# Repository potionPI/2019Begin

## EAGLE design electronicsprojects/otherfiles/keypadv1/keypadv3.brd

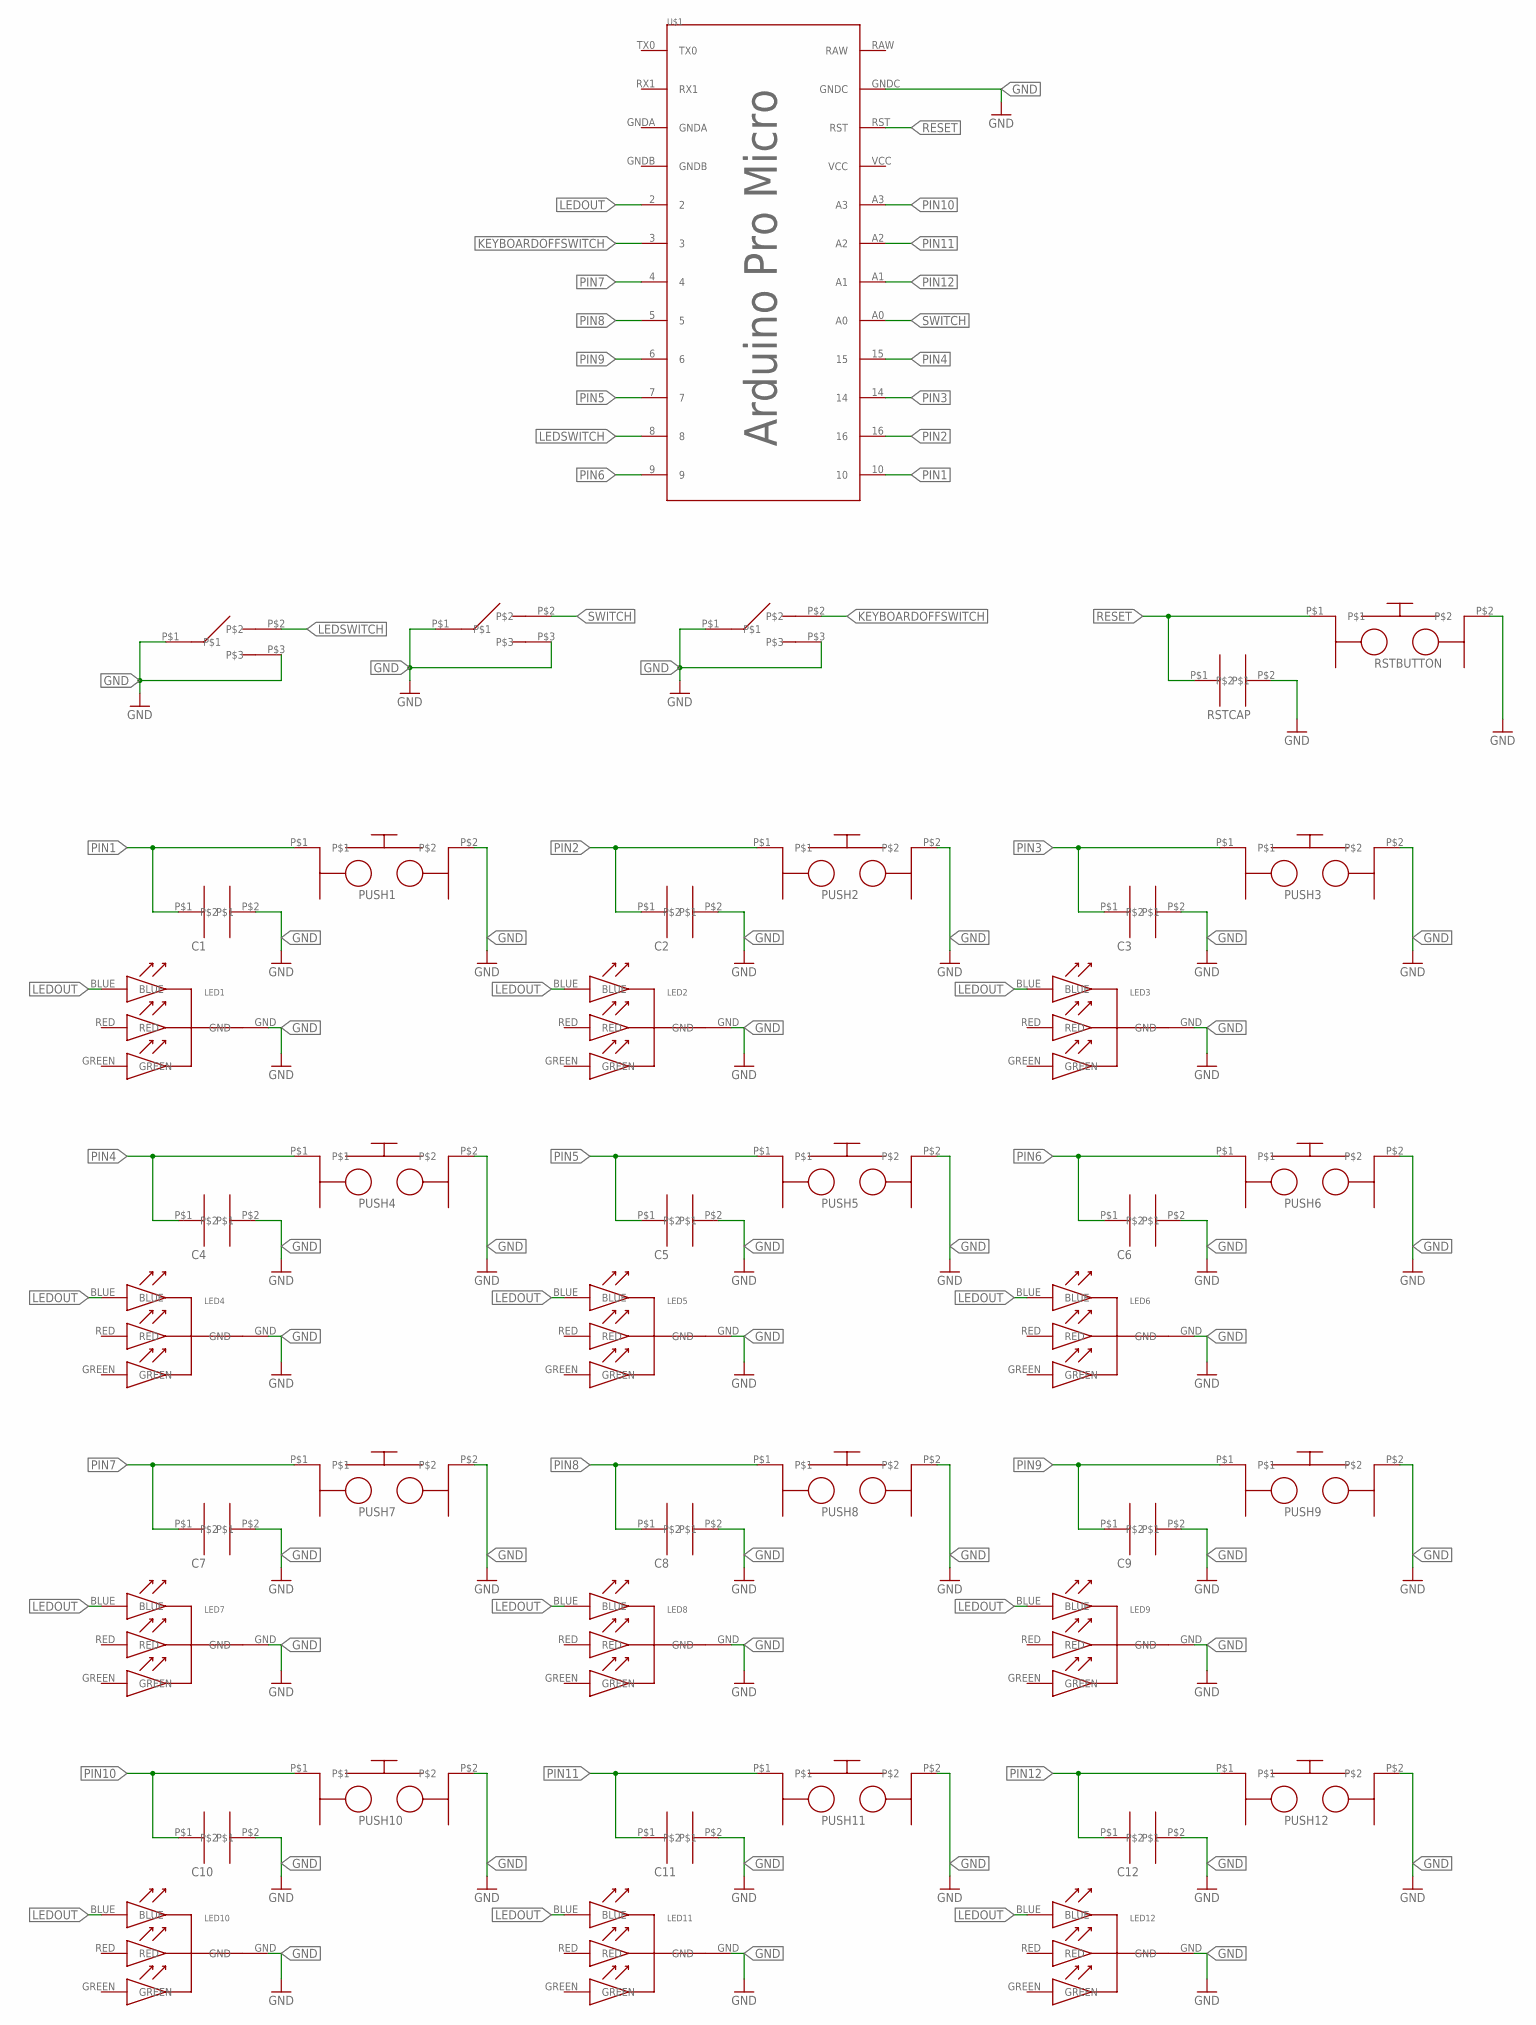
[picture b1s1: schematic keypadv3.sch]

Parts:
C1, C2, C3, C4, C5, C6, C7, C8, C9, C10, C11, C12: CERAMICCAP; CERAMICCAPACITOR
LED1, LED2, LED3, LED4, LED5, LED6, LED7, LED8, LED9, LED10, LED11, LED12: RGBLED5MMCOMMONCATHODE; LEADSPREAD
PUSH1, PUSH2, PUSH3, PUSH4, PUSH5, PUSH6, PUSH7, PUSH8, PUSH9, PUSH10, PUSH11, PUSH12: 2LEADS
RSTBUTTON: 2LEADS
RSTCAP: CERAMICCAP; CERAMICCAPACITOR
SWITCH1, SWITCH2, SWITCH3: SWITCH; THREEPINSWITCH
U$1: ARDUINOPROMICRO; ARDUINO_PRO_MICRO

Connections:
GND: C1.P$2, C2.P$2, C3.P$2, C4.P$2, C5.P$2, C6.P$2, C7.P$2, C8.P$2, C9.P$2, C10.P$2, C11.P$2, C12.P$2, LED1.GND, LED2.GND, LED3.GND, LED4.GND, LED5.GND, LED6.GND, LED7.GND, LED8.GND, LED9.GND, LED10.GND, LED11.GND, LED12.GND, PUSH1.P$2, PUSH2.P$2, PUSH3.P$2, PUSH4.P$2, PUSH5.P$2, PUSH6.P$2, PUSH7.P$2, PUSH8.P$2, PUSH9.P$2, PUSH10.P$2, PUSH11.P$2, PUSH12.P$2, RSTBUTTON.P$2, RSTCAP.P$2, SWITCH1.P$1, SWITCH1.P$3, SWITCH2.P$1, SWITCH2.P$3, SWITCH3.P$1, SWITCH3.P$3, U$1.GNDC
KEYBOARDOFFSWITCH: SWITCH2.P$2, U$1.3
LEDOUT: LED1.BLUE, LED2.BLUE, LED3.BLUE, LED4.BLUE, LED5.BLUE, LED6.BLUE, LED7.BLUE, LED8.BLUE, LED9.BLUE, LED10.BLUE, LED11.BLUE, LED12.BLUE, U$1.2
LEDSWITCH: SWITCH1.P$2, U$1.8
PIN1: C1.P$1, PUSH1.P$1, U$1.10
PIN2: C2.P$1, PUSH2.P$1, U$1.16
PIN3: C3.P$1, PUSH3.P$1, U$1.14
PIN4: C4.P$1, PUSH4.P$1, U$1.15
PIN5: C5.P$1, PUSH5.P$1, U$1.7
PIN6: C6.P$1, PUSH6.P$1, U$1.9
PIN7: C7.P$1, PUSH7.P$1, U$1.4
PIN8: C8.P$1, PUSH8.P$1, U$1.5
PIN9: C9.P$1, PUSH9.P$1, U$1.6
PIN10: C10.P$1, PUSH10.P$1, U$1.A3
PIN11: C11.P$1, PUSH11.P$1, U$1.A2
PIN12: C12.P$1, PUSH12.P$1, U$1.A1
RESET: RSTBUTTON.P$1, RSTCAP.P$1, U$1.RST
SWITCH: SWITCH3.P$2, U$1.A0

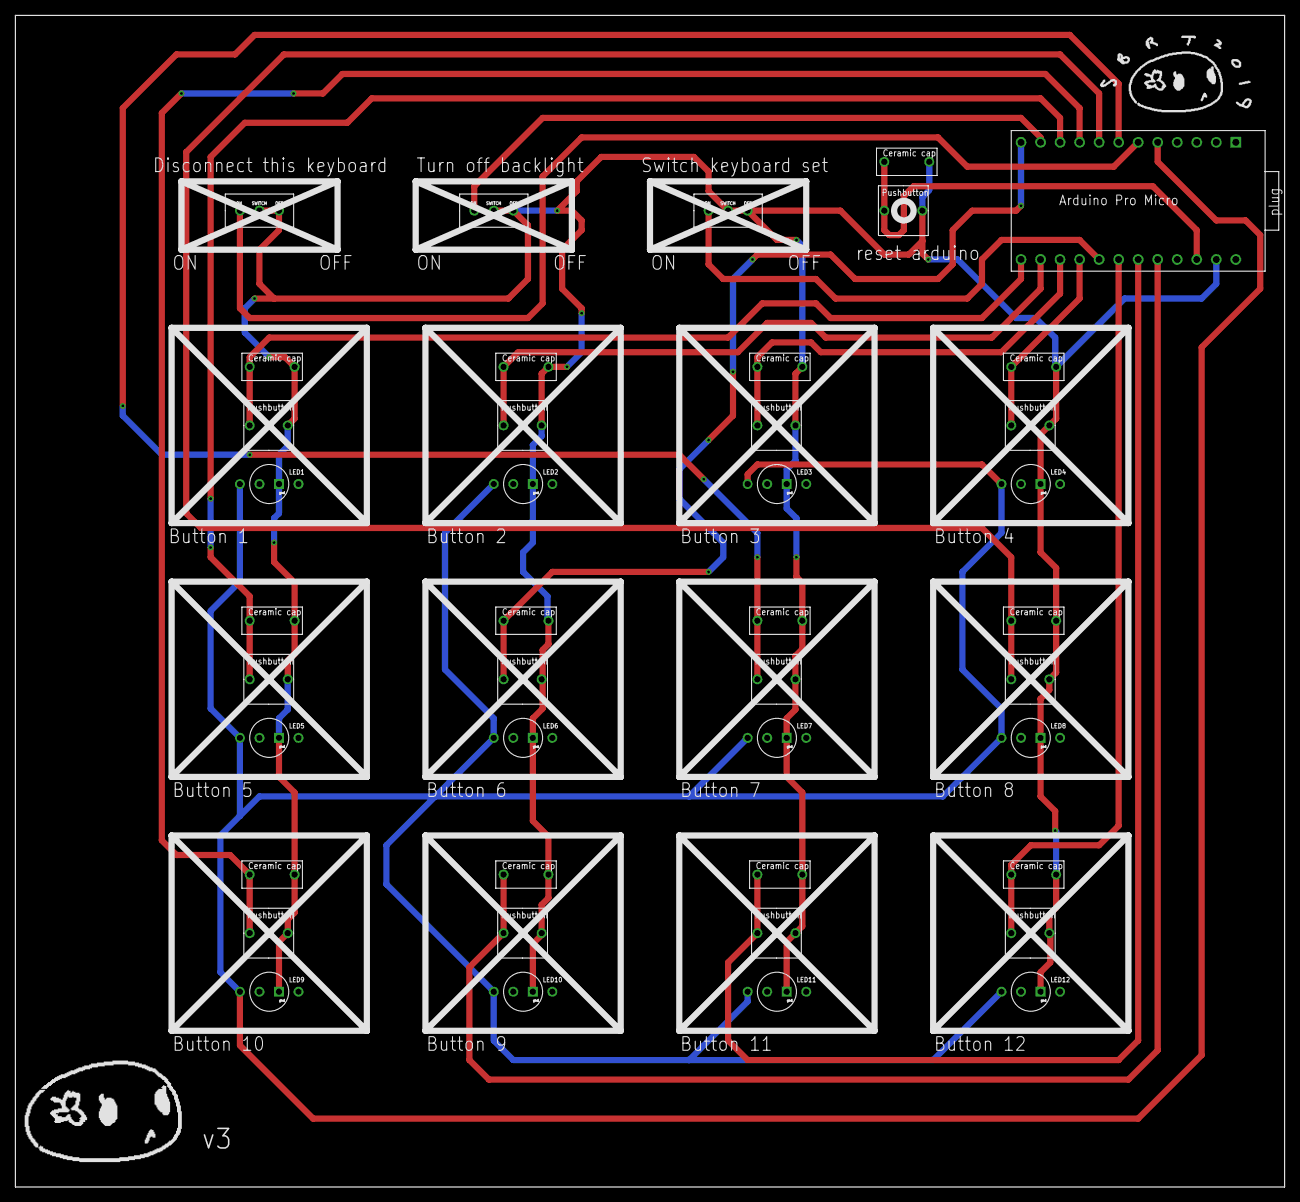
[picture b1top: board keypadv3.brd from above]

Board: 2 copper layers, 165.1 x 152.4 mm, 42 parts (0 on the bottom side), 18 nets.

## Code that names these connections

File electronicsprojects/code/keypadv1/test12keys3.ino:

#include <Keyboard.h>

#define PIN1  10
#define PIN2  16
#define PIN3  14
#define PIN4  15
#define PIN5  7
#define PIN6  9
#define PIN7  4
#define PIN8  5
#define PIN9  6
#define PIN10 A3 
#define PIN11 A2
#define PIN12 A1

#define SWITCH  A0
#define LEDSWITCH 8
#define LEDOUT 2
#define KEYBOARDOFFSWITCH 3

int readyRelease1 = 0;
int readyRelease2 = 0;
int readyRelease3 = 0;
int readyRelease4 = 0;
int readyRelease5 = 0;
int readyRelease6 = 0;
int readyRelease7 = 0;
int readyRelease8 = 0;
int readyRelease9 = 0;
int readyRelease10 = 0;
int readyRelease11 = 0;
int readyRelease12 = 0;

void pressReleaseCheck() { // Keypads set 1 is currently numbers. Edit both Keyboard.press(es) and Keyboard.release(s) on pin to change what pressing on button does
  if (digitalRead(PIN1) == LOW) {
    Keyboard.press('1');
    readyRelease1 = 1;
  }
  if (digitalRead(PIN2) == LOW) {
    Keyboard.press('2');
    readyRelease2 = 1;
  }
  if (digitalRead(PIN3) == LOW) {
    Keyboard.press('3');
    readyRelease3 = 1;
  }

  if (digitalRead(PIN4) == LOW) {
    Keyboard.press('4');
    readyRelease4 = 1;
  }
  if (digitalRead(PIN5) == LOW) {
    Keyboard.press('5');
    readyRelease5 = 1;
  }
  if (digitalRead(PIN6) == LOW) {
    Keyboard.press('6');
    readyRelease6 = 1;
  }

  if (digitalRead(PIN7) == LOW) {
    Keyboard.press('7');
    readyRelease7 = 1;
  }
  if (digitalRead(PIN8) == LOW) {
    Keyboard.press('8');
    readyRelease8 = 1;
  }
  if (digitalRead(PIN9) == LOW) {
    Keyboard.press('9');
    readyRelease9 = 1;
  }

  if (digitalRead(PIN10) == LOW) {
    Keyboard.press('0');
    readyRelease10 = 1;
  }
  if (digitalRead(PIN11) == LOW) {
    Keyboard.press(KEY_LEFT_CTRL);
    Keyboard.press('c');
    readyRelease11 = 1;
  }
  if (digitalRead(PIN12) == LOW) {
    Keyboard.press(KEY_LEFT_CTRL);
    Keyboard.press('v');
    readyRelease12 = 1;
  }

  ///

  if (readyRelease1 && digitalRead(PIN1)) {
    Keyboard.release('1');
    readyRelease1 = 0;
  }
  if (readyRelease2 && digitalRead(PIN2)) {
    Keyboard.release('2');
    readyRelease2 = 0;
  }
  if (readyRelease3 && digitalRead(PIN3)) {
    Keyboard.release('3');
    readyRelease3 = 0;
  }

  if (readyRelease4 && digitalRead(PIN4)) {
    Keyboard.release('4');
    readyRelease4 = 0;
  }
  if (readyRelease5 && digitalRead(PIN5)) {
    Keyboard.release('5');
    readyRelease5 = 0;
  }
  if (readyRelease6 && digitalRead(PIN6)) {
    Keyboard.release('6');
    readyRelease6 = 0;
  }

  if (readyRelease7 && digitalRead(PIN7)) {
    Keyboard.release('7');
      readyRelease7 = 0;
  }
  if (readyRelease8 && digitalRead(PIN8)) {
    Keyboard.release('8');
    readyRelease8 = 0;
  }
  if (readyRelease9 && digitalRead(PIN9)) {
    Keyboard.release('9');
    readyRelease9 = 0;
  }

  if (readyRelease10 && digitalRead(PIN10)) {
     Keyboard.release('0');
     readyRelease10 = 0;
  }
  if (readyRelease11 && digitalRead(PIN11)) {
    Keyboard.release(KEY_LEFT_CTRL);
    Keyboard.release('c');
    readyRelease11 = 0;
  }
  if (readyRelease12 && digitalRead(PIN12)) {
    Keyboard.release(KEY_LEFT_CTRL);
    Keyboard.release('v');
    readyRelease12 = 0;
  }
}


void pressReleaseCheck2() { // Keypads set 2 is currently f1-f12. Edit both Keyboard.press(es) and Keyboard.release(s) on pin to change what pressing on button does
  if (digitalRead(PIN1) == LOW) {
    Keyboard.press(KEY_F1);
    while(digitalRead(PIN1) == LOW){}
    readyRelease1 = 1;
  }
  if (digitalRead(PIN2) == LOW) {
    Keyboard.press(KEY_F2);
    while(digitalRead(PIN2) == LOW){}
    readyRelease2 = 1;
  }
  if (digitalRead(PIN3) == LOW) {
    Keyboard.press(KEY_F3);
    while(digitalRead(PIN3) == LOW){}
    readyRelease3 = 1;
  }

  if (digitalRead(PIN4) == LOW) {
    Keyboard.press(KEY_F4);
    while(digitalRead(PIN4) == LOW){}
    readyRelease4 = 1;
  }
  if (digitalRead(PIN5) == LOW) {
    Keyboard.press(KEY_F5);
    while(digitalRead(PIN5) == LOW){}
    readyRelease5 = 1;
  }
  if (digitalRead(PIN6) == LOW) {
    Keyboard.press(KEY_F6);
    while(digitalRead(PIN6) == LOW){}
    readyRelease6 = 1;
  }

  if (digitalRead(PIN7) == LOW) {
    Keyboard.press(KEY_F7);
    while(digitalRead(PIN7) == LOW){}
    readyRelease7 = 1;
  }
  if (digitalRead(PIN8) == LOW) {
    Keyboard.press(KEY_F8);
    while(digitalRead(PIN8) == LOW){}
    readyRelease8 = 1;
  }
  if (digitalRead(PIN9) == LOW) {
    Keyboard.press(KEY_F9);
    while(digitalRead(PIN9) == LOW){}
    readyRelease9 = 1;
  }

  if (digitalRead(PIN10) == LOW) {
    Keyboard.press(KEY_F10);
    while(digitalRead(PIN10) == LOW){}
    readyRelease10 = 1;
  }
  if (digitalRead(PIN11) == LOW) {
    Keyboard.press(KEY_F11);
    while(digitalRead(PIN11) == LOW){}
    readyRelease11 = 1;
  }
  if (digitalRead(PIN12) == LOW) {
    Keyboard.press(KEY_F12);
    while(digitalRead(PIN12) == LOW){}
    readyRelease12 = 1;
  }

  ///

  if (readyRelease1 && digitalRead(PIN1)) {
    Keyboard.release(KEY_F1);
    readyRelease1 = 0;
  }
  if (readyRelease2 && digitalRead(PIN2)) {
    Keyboard.release(KEY_F2);
    readyRelease2 = 0;
  }
  if (readyRelease3 && digitalRead(PIN3)) {
    Keyboard.release(KEY_F3);
    readyRelease3 = 0;
  }

  if (readyRelease4 && digitalRead(PIN4)) {
    Keyboard.release(KEY_F4);
    readyRelease4 = 0;
  }
  if (readyRelease5 && digitalRead(PIN5)) {
    Keyboard.release(KEY_F5);
    readyRelease5 = 0;
  }
  if (readyRelease6 && digitalRead(PIN6)) {
    Keyboard.release(KEY_F6);
    readyRelease6 = 0;
  }

  if (readyRelease7 && digitalRead(PIN7)) {
    Keyboard.release(KEY_F7);
    readyRelease7 = 0;
  }
  if (readyRelease8 && digitalRead(PIN8)) {
    Keyboard.release(KEY_F8);
    readyRelease8 = 0;
  }
  if (readyRelease9 && digitalRead(PIN9)) {
    Keyboard.release(KEY_F9);
    readyRelease9 = 0;
  }

  if (readyRelease10 && digitalRead(PIN10)) {
     Keyboard.release(KEY_F10);
     readyRelease10 = 0;
  }
  if (readyRelease11 && digitalRead(PIN11)) {
    Keyboard.release(KEY_F11);
    readyRelease11 = 0;
  }
  if (readyRelease12 && digitalRead(PIN12)) {
    Keyboard.release(KEY_F12);
    readyRelease12 = 0;
  }
}


//
void setup() {
  pinMode(PIN1, INPUT_PULLUP);
  pinMode(PIN2, INPUT_PULLUP);
  pinMode(PIN3, INPUT_PULLUP);
  pinMode(PIN4, INPUT_PULLUP);
  pinMode(PIN5, INPUT_PULLUP);
  pinMode(PIN6, INPUT_PULLUP);
  pinMode(PIN7, INPUT_PULLUP);
  pinMode(PIN8, INPUT_PULLUP);
  pinMode(PIN9, INPUT_PULLUP);
  pinMode(PIN10, INPUT_PULLUP);
  pinMode(PIN11, INPUT_PULLUP);
  pinMode(PIN12, INPUT_PULLUP);
  pinMode(SWITCH, INPUT_PULLUP);
  pinMode(LEDSWITCH, INPUT_PULLUP);
  pinMode(LEDOUT, OUTPUT);
  pinMode(KEYBOARDOFFSWITCH, INPUT_PULLUP);
  
  Keyboard.begin();
}
void loop() {
  if (digitalRead(SWITCH)) {
    pressReleaseCheck();  // Keypads set 1
  } else {
    pressReleaseCheck2(); // Keypads set 2
  }
  if (digitalRead(LEDSWITCH)) { // Switch LEDS on or off
    digitalWrite(LEDOUT, HIGH);
  } else {
    digitalWrite(LEDOUT, LOW);
  }

  if (digitalRead(KEYBOARDOFFSWITCH)) {
    Keyboard.releaseAll();
    Keyboard.end();
    while(digitalRead(KEYBOARDOFFSWITCH)) {
    }
    Keyboard.begin();
  }
  
}

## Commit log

2019-08-03 testing download
2019-08-03 added resouces
2019-08-10 update with Eagle videos
